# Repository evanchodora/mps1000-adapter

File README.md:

# Dell MPS1000 Power Supply Adapter

PCB design for a custom PCB to allow for repurposing the Dell MPS600 & MPS1000 power supplies for powering 48VDC rackmount equipment with screw terminal outputs.

See my website ([garageprotocols.com](https://garageprotocols.com/projects/electronics/48v_rack_power/)) for more details.

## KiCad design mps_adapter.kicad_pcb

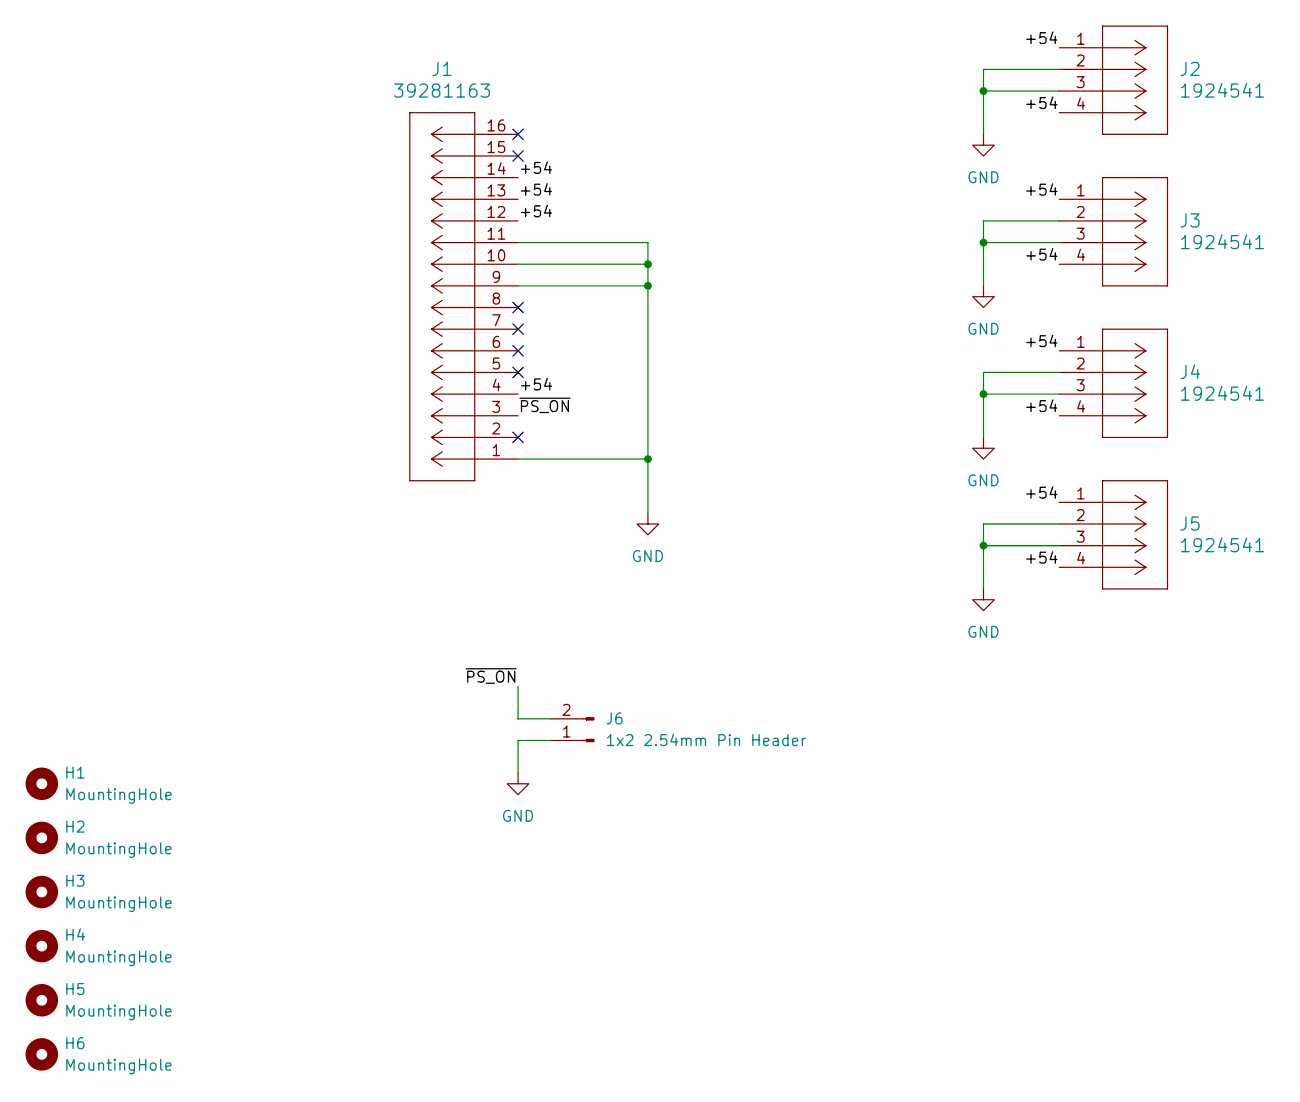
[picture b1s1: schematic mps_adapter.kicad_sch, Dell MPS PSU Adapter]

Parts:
H1, H2, H3, H4, H5, H6: MountingHole; MountingHole_2.7mm_M2.5_ISO7380
J1: 39281163; CONN_SD-5566-002_16_MOL
J2, J3, J4, J5: 1924541; CONN_1924541
J6: 1x2 2.54mm Pin Header; PinHeader_1x02_P2.54mm_Vertical

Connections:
/+54: J1.4, J1.12, J1.13, J1.14, J2.1, J2.4, J3.1, J3.4, J4.1, J4.4, J5.1, J5.4
/~PS_ON: J1.3, J6.2
GND: J1.1, J1.9, J1.10, J1.11, J2.2, J2.3, J3.2, J3.3, J4.2, J4.3, J5.2, J5.3, J6.1

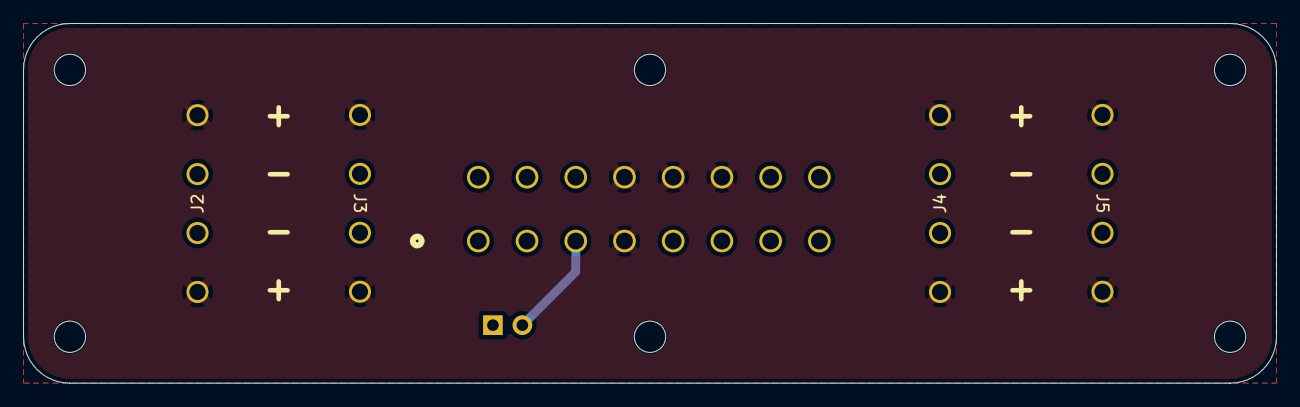
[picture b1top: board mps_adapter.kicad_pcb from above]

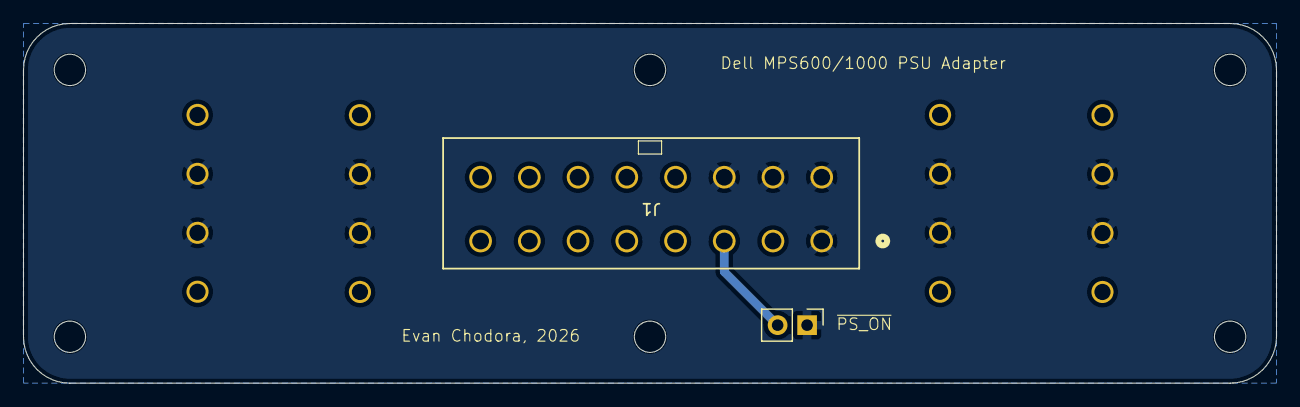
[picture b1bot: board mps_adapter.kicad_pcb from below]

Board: 2 copper layers, 108.0 x 31.0 mm, 12 parts (2 on the bottom side), 3 nets.

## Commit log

2026-05-17 Added license
2026-05-17 Created README
